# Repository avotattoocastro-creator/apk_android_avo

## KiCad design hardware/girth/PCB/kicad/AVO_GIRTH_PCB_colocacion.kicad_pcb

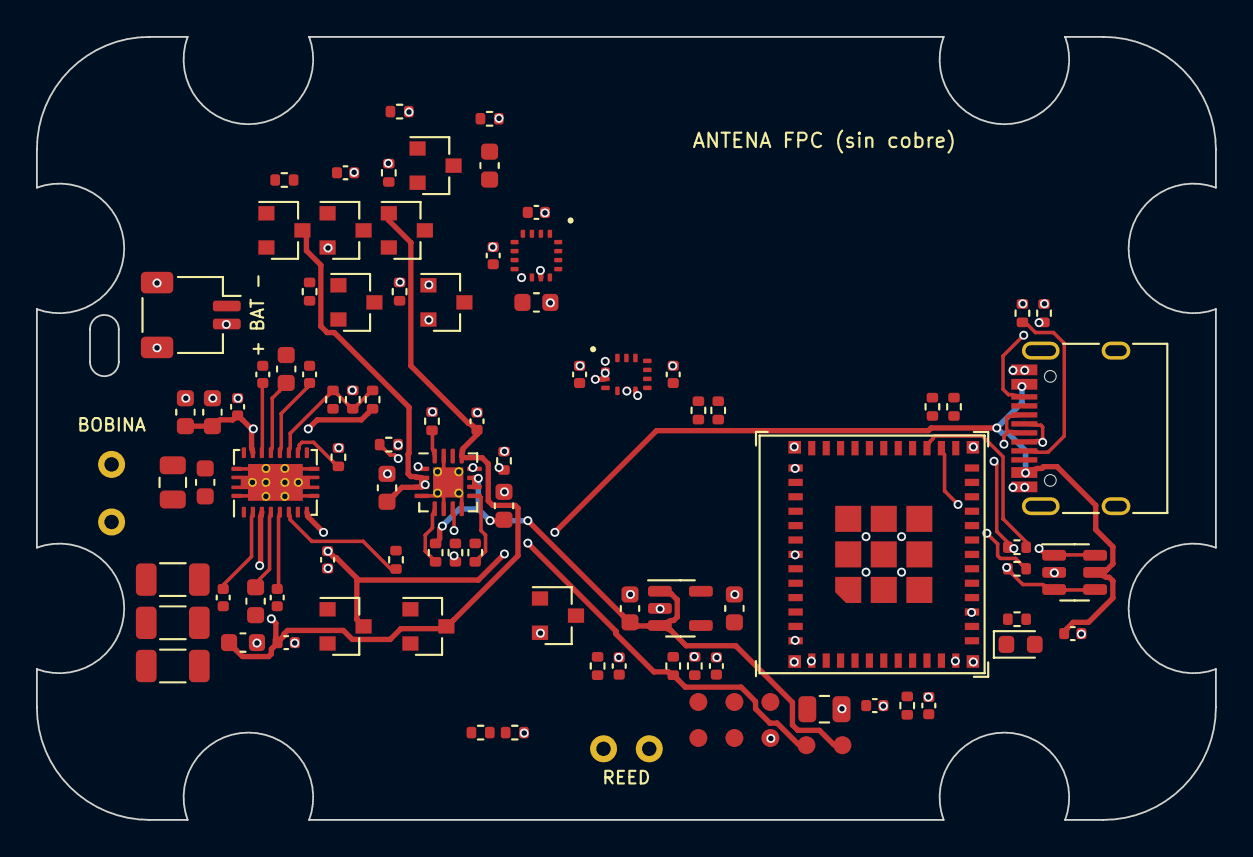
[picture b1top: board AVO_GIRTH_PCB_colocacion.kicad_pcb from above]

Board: 4 copper layers, 65.5 x 43.5 mm, 98 parts (0 on the bottom side), 55 nets.

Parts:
C1, C2: 100n C0G 50V; C_1206_3216Metric
C3: 47n C0G 50V; C_1206_3216Metric
C4: 2n2 C0G 50V; C_0805_2012Metric
C5: 1n C0G 50V; C_0603_1608Metric
C6, C9, C33: 10n 50V; C_0402_1005Metric
C7, C10: 470n 25V; C_0603_1608Metric
C8, C11: 22n 50V; C_0402_1005Metric
C12, C13, C15, C19, C20, C21, C22: 10u 25V; C_0603_1608Metric
C14, C16, C24, C27, C28, C31, C34: 100n; C_0402_1005Metric
C17, C18, C25, C26, C29: 1u; C_0402_1005Metric
C23: 22u 10V; C_0805_2012Metric
C30: 10u 6V3; C_0603_1608Metric
C40: 2u2; C_0603_1608Metric
C41: 220n; C_0402_1005Metric
D1: LED rojo; LED_0603_1608Metric
D10, D11, D12, D13: BAV70; SOT-23
J1: USB-C 16P; USB_C_Receptacle_HRO_TYPE-C-31-M-12
J2: BATERÍA 1S; JST_SH_SM02B-SRSS-TB_1x02-1MP_P1.00mm_Horizontal
L1: BOBINA Qi (1); WirePad_D1.5_Drill0.8
L2: BOBINA Qi (2); WirePad_D1.5_Drill0.8
Q1, Q2, Q10: AO3401A; SOT-23
Q11: AO3400A; SOT-23
Q16: 2N7002; SOT-23
R1: 330R; R_0402_1005Metric
R2: 200R; R_0402_1005Metric
R3: 20k; R_0402_1005Metric
R4, R8, R9, R10, R31, R43, R49: 100k; R_0402_1005Metric
R6, R7: 3k3; R_0402_1005Metric
R11, R12, R13: 10k; R_0402_1005Metric
R15: 1k; R_0402_1005Metric
R16, R17: 5k1; R_0402_1005Metric
R18, R19: 22R; R_0402_1005Metric
R20, R21: 4k7; R_0402_1005Metric
R32, R33, R40, R45, R50: 1M; R_0402_1005Metric
R41, R42: 10M; R_0402_1005Metric
R44: 220R; R_0402_1005Metric
RT1, RT2: NTC 10k B3380; R_0402_1005Metric
SW1: REED (1); WirePad_D1.5_Drill0.8
SW2: REED (2); WirePad_D1.5_Drill0.8
TP1: EN; TestPoint_Pad_D1.0mm
TP2: BOOT; TestPoint_Pad_D1.0mm
TP3: GND; TestPoint_Pad_D1.0mm
TP4: TXD0; TestPoint_Pad_D1.0mm
TP5: RXD0; TestPoint_Pad_D1.0mm
TP6: 3V3; TestPoint_Pad_D1.0mm
TP7: VBAT; TestPoint_Pad_D1.0mm
TP8: VSYS; TestPoint_Pad_D1.0mm
U1: BQ51013BRHLR; Texas_VQFN-RHL-20_ThermalVias
U2: BQ24072RGTR; VQFN-16-1EP_3x3mm_P0.5mm_EP1.68x1.68mm_ThermalVias
U3: RT9080-33GJ5; SOT-23-5
U4: ESP32-C3-MINI-1U-N4; ESP32-C3-MINI-1U
U5: LSM6DS3TR-C; ST_LGA-14L_2.5x3mm_P0.5mm
U6: USBLC6-2SC6; SOT-23-6
U7: MMC5983MA; MEMSIC_MMC5983MA_LGA-16_3x3mm_P0.5mm

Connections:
+3V3: C22.1, C23.1, C24.1, C27.1, C28.1, C29.1, C31.1, D1.2, R4.2, R9.2, R10.2, R11.2, R12.2, R13.2, R20.2, R21.2, R31.2, TP6.1, U3.5, U4.3, U5.5, U5.8, U5.12, U7.2, U7.4, U7.13
AD_SRC: Q1.2, Q2.2
BAT_ADC: C34.1, R32.2, R33.1, U4.6
BAT_RAW: J2.1, Q10.2, R40.1, SW2.1
BOOT: R12.1, TP2.1, U4.23
CC1: J1.A5, R16.1
CC2: J1.B5, R17.1
CHG_EN2: R8.1, U2.5
CHG_ILIM: R7.1, U2.12
CHG_ISET: R6.1, U2.16
CHG_PG: R9.1, U2.7, U4.18
CHG_STAT: R10.1, U2.9, U4.21
CHG_TS: RT2.1, U2.1
EN: C25.1, R11.1, TP1.1, U4.8
GND: C12.2, C13.2, C14.2, C15.2, C16.2, C17.2, C18.2, C19.2, C20.2, C21.2, C22.2, C23.2, C24.2, C25.2, C26.2, C27.2, C28.2, C29.2, C30.2, C31.2, C33.2, C34.2, C41.2, D13.1, D13.2, J1.A1, J1.A12, J1.B1, J1.B12, J1.S1, J2.2, J2.MP, Q11.2, Q16.2, R2.2, R6.2, R7.2, R16.2, R17.2, R33.2, R41.2, R42.2, R43.2, R45.2, R50.2, RT1.2, RT2.2, TP3.1, U1.1, U1.10, U1.11, U1.20, U1.21, U2.4, U2.6, U2.8, U2.15, U2.17, U3.2, U4.1, U4.2, U4.11, U4.14, U4.36, U4.37, U4.38, U4.39, U4.40, U4.41, U4.42, U4.43, U4.44, U4.45, U4.46, U4.47, U4.48, U4.49, U4.50, U4.51, U4.52, U4.53, U5.1, U5.2, U5.3, U5.6, U5.7, U6.2, U7.9, U7.11
I2C_SCL: R21.1, U4.5, U5.13, U7.1
I2C_SDA: R20.1, U4.20, U5.14, U7.16
IMU_INT: U4.12, U5.4
LED: R13.1, R15.1, U4.22
LED_K: D1.1, R15.2
MAG_CAP: C30.1, U7.10
PWR_G: C41.1, D10.3, D11.3, Q11.1, R42.1
PWR_HOLD: D10.2, R43.1, U4.19
PWR_PG: Q10.1, Q11.3, R40.2
QI_AC1: C1.2, C2.2, C3.2, C4.1, C5.1, C6.2, C7.2, C8.2, U1.2
QI_AC2: C4.2, C5.2, C9.2, C10.2, C11.2, L2.1, U1.19
QI_ADEN: Q1.1, Q2.1, U1.8
QI_BOOT1: C6.1, U1.3
QI_BOOT2: C9.1, U1.17
QI_CHG: R4.1, U1.7, U4.16
QI_CLAMP1: C7.1, U1.5
QI_CLAMP2: C10.1, U1.16
QI_COIL1: C1.1, C2.1, C3.1, L1.1
QI_COMM1: C8.1, U1.6
QI_COMM2: C11.1, U1.15
QI_FOD: R1.2, R2.1, R3.2, U1.14
QI_ILIM: R1.1, U1.12
QI_RECT: C12.1, C13.1, C14.1, R3.1, U1.18
QI_TS: RT1.1, U1.13
REED: C33.1, Q16.3, R31.1, U4.13
REED_C: D12.3, R44.1, R45.1
REED_CR: C40.1, R44.2
REED_G: Q16.1, R49.2, R50.1
REED_HI: D12.1, D12.2, R49.1, SW1.1
REED_PULSE: C40.2, D11.1, D11.2, D13.3, R41.1
U0RX: TP5.1, U4.30
U0TX: TP4.1, U4.31
USB_DM: R19.2, U4.26
USB_DM_C: J1.A7, J1.B7, R19.1, U6.3, U6.4
USB_DP: R18.2, U4.27
USB_DP_C: J1.A6, J1.B6, R18.1, U6.1, U6.6
VBAT: C20.1, Q10.3, R32.1, TP7.1, U2.2, U2.3
VBUS: C17.1, C26.1, J1.A4, J1.A9, J1.B4, J1.B9, Q1.3, U1.9, U6.5
VIN5: C15.1, C16.1, C18.1, D10.1, Q2.3, U1.4, U2.13
VSYS: C19.1, C21.1, R8.2, TP8.1, U2.10, U2.11, U3.1, U3.3

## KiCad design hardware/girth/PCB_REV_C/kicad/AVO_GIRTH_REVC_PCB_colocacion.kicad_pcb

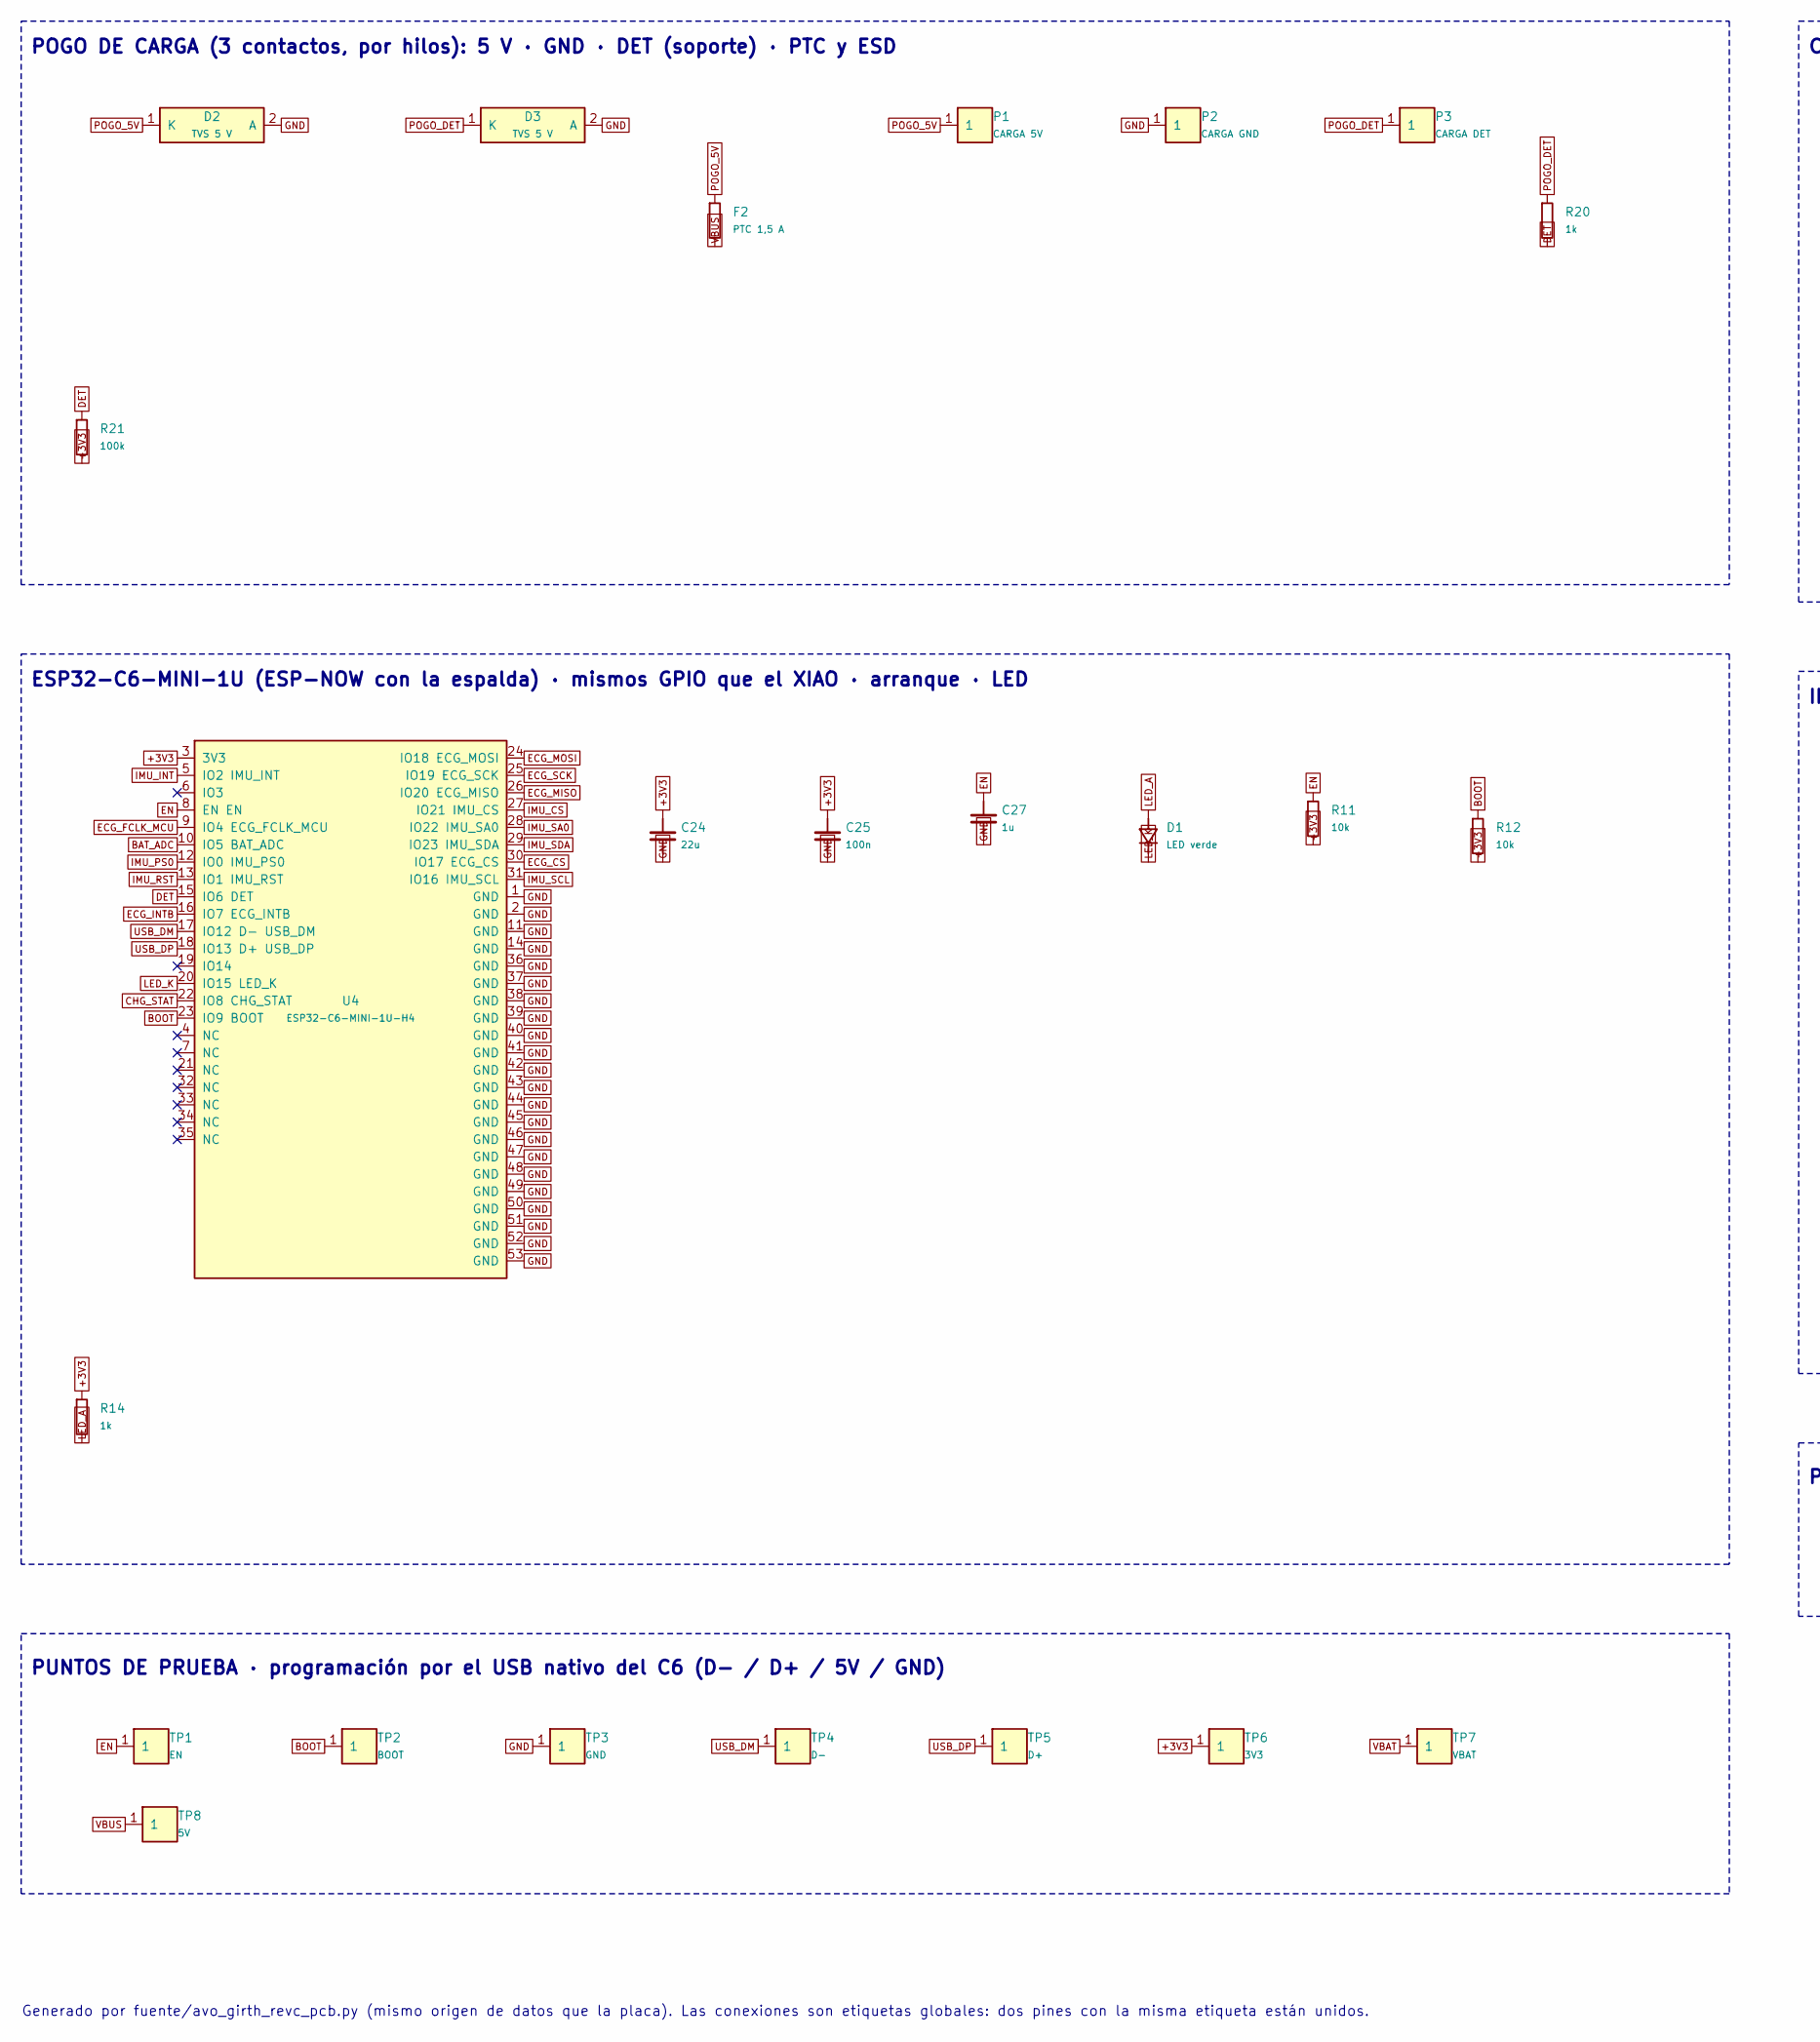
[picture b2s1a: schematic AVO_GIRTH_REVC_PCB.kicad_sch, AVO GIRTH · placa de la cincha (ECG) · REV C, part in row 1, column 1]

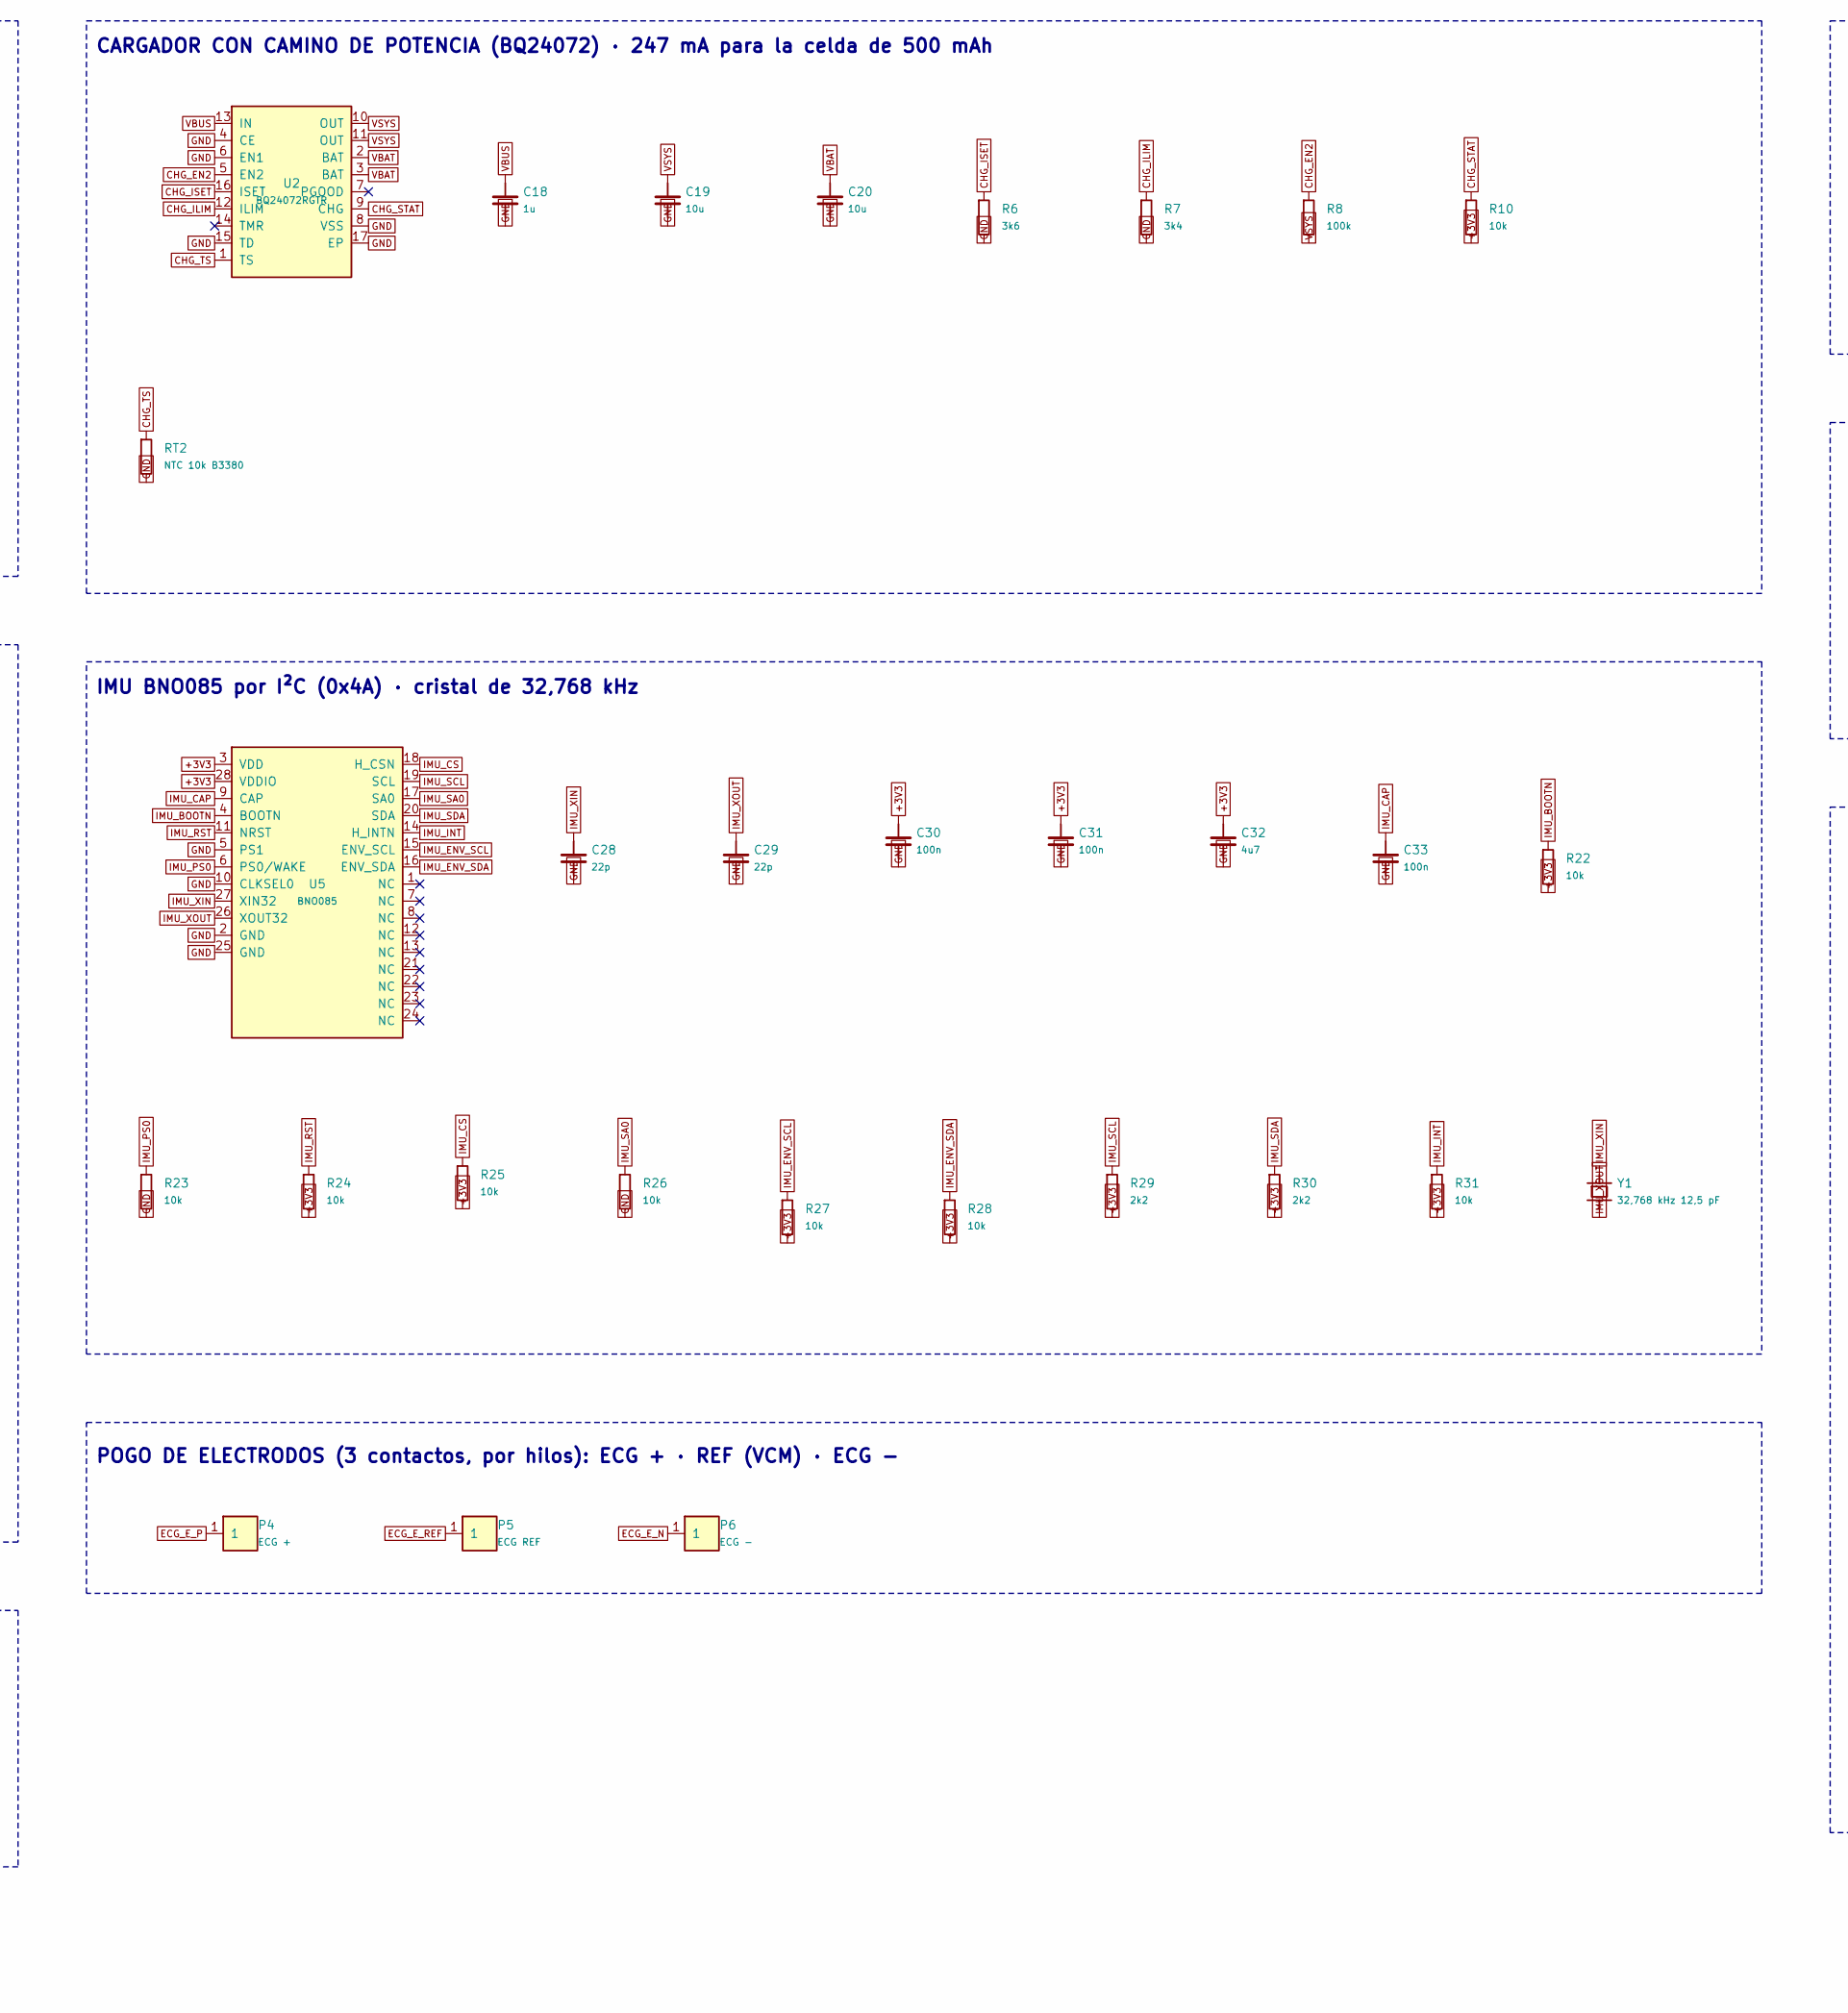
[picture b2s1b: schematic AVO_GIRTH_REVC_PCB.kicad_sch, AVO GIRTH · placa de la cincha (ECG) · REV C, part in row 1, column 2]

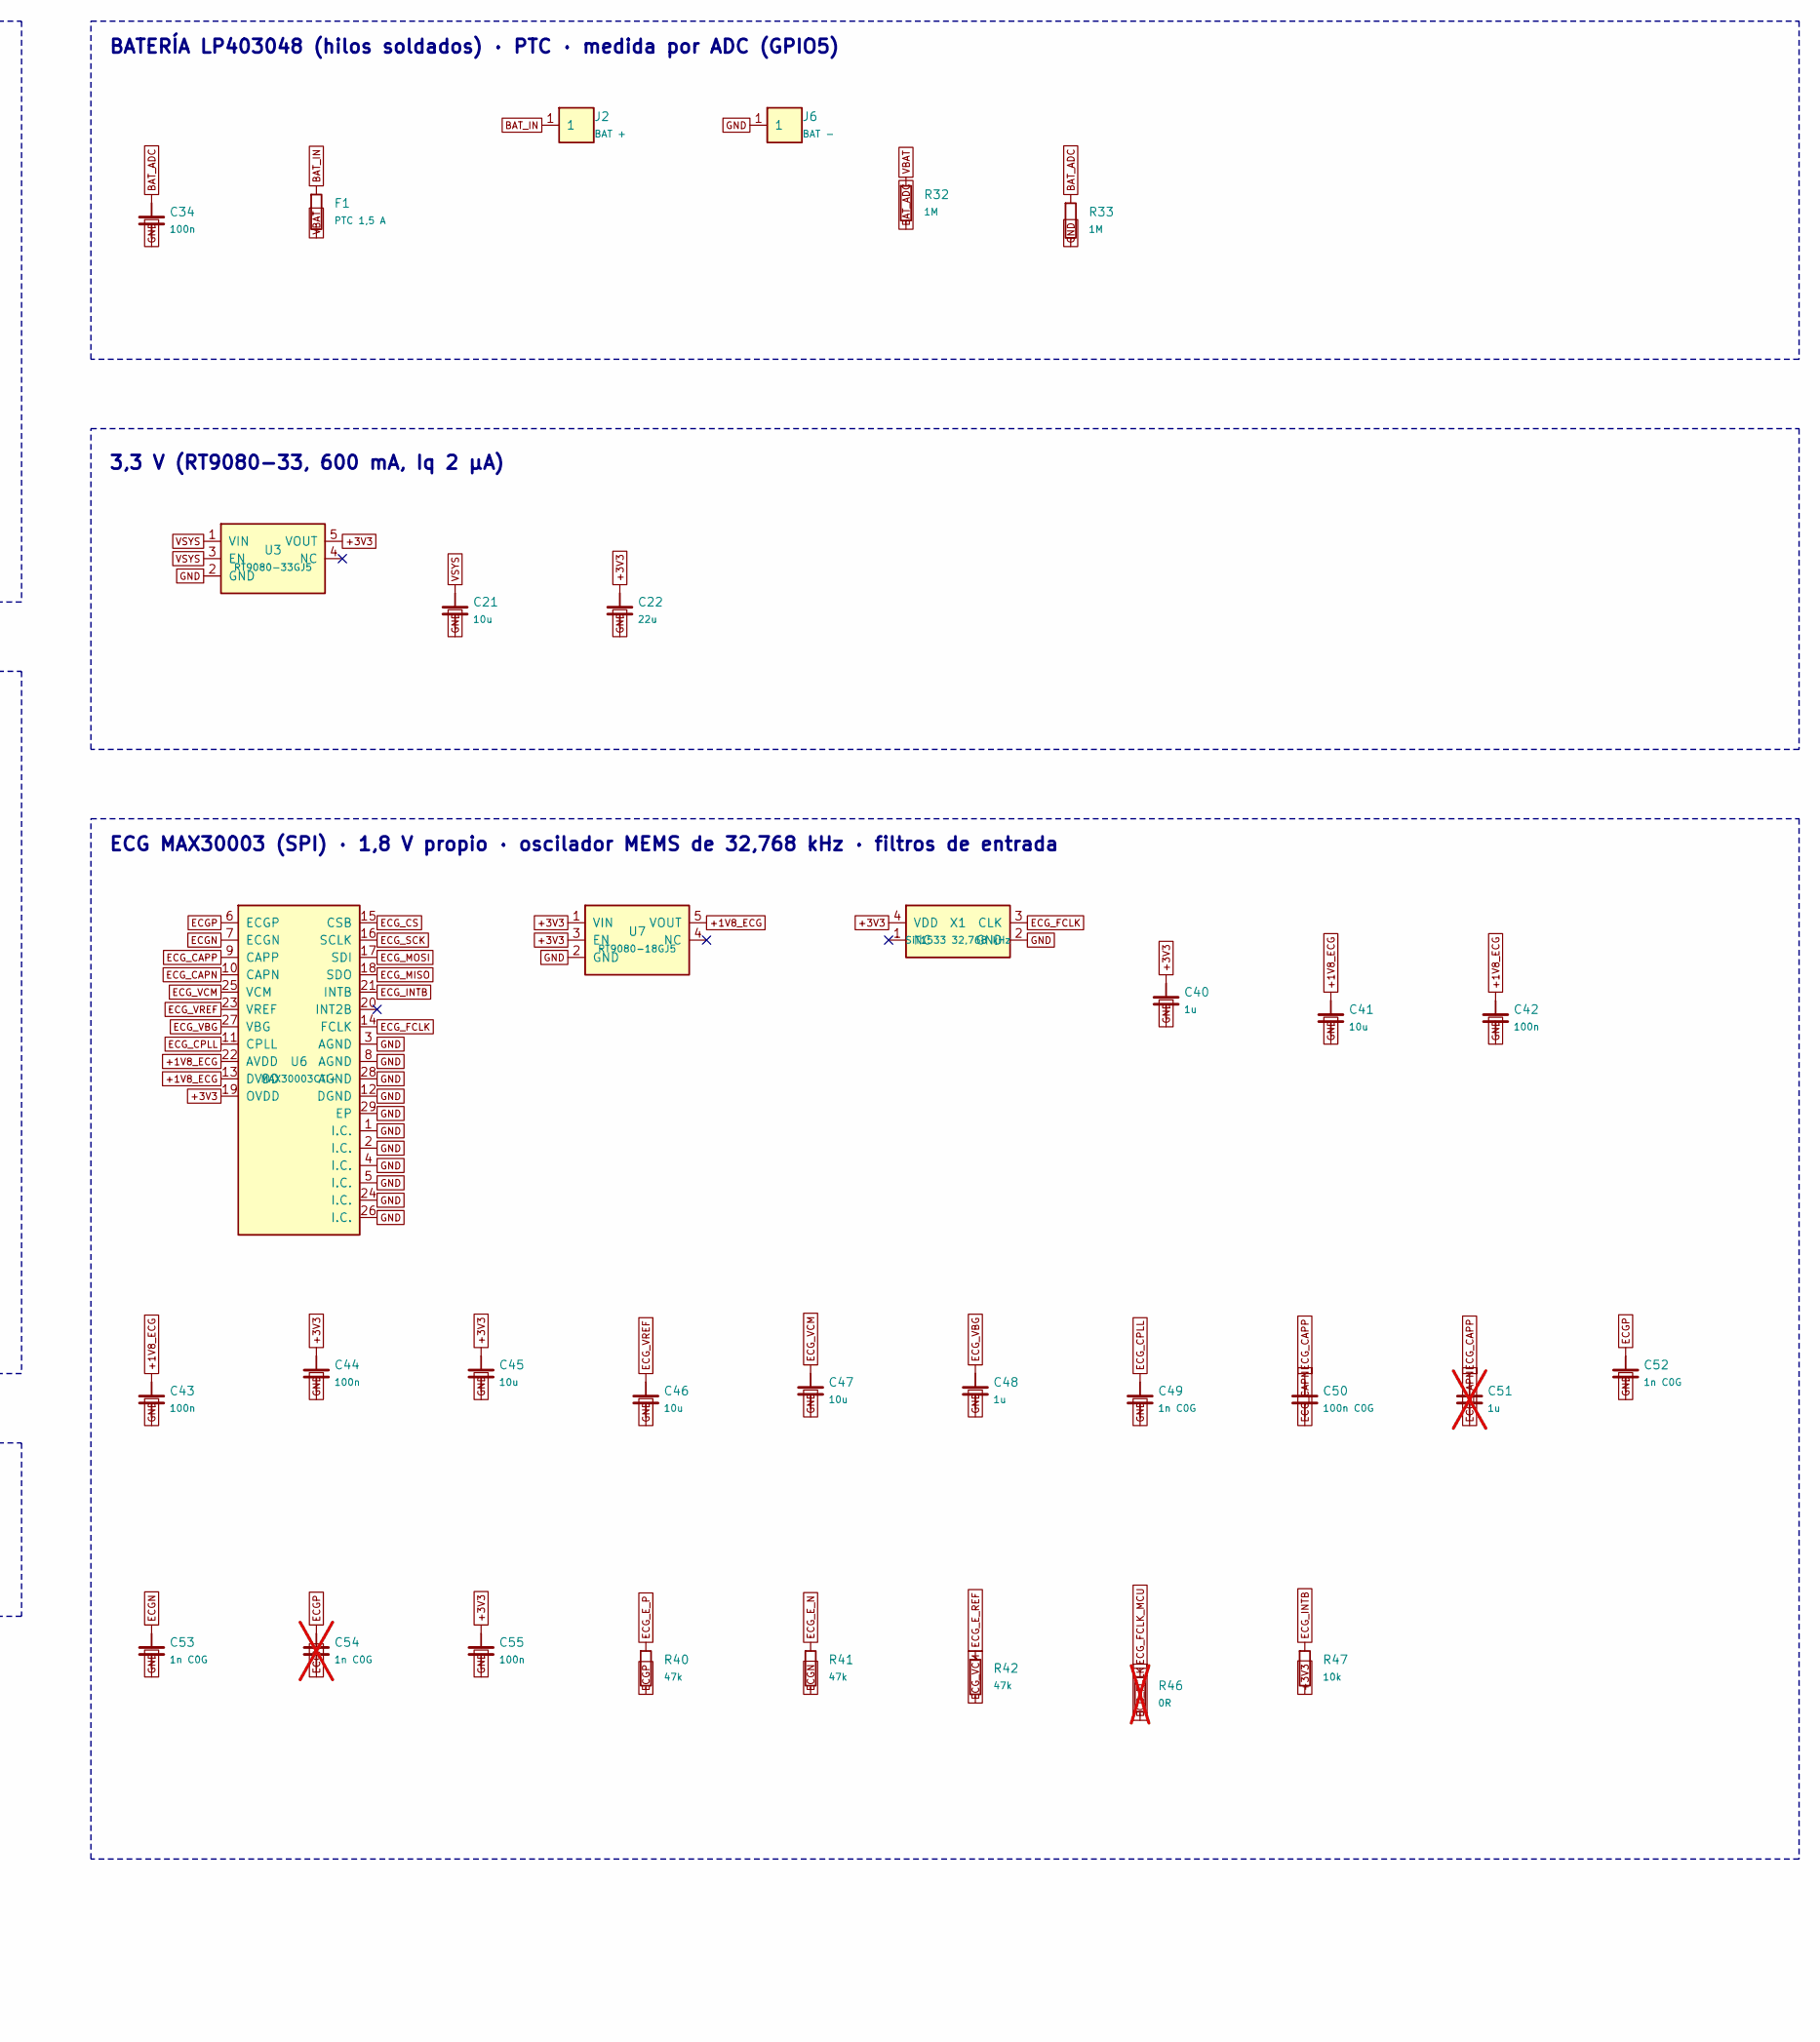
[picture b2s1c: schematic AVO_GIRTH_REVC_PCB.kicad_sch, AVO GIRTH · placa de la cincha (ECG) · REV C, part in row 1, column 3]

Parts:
C18, C27, C40, C48: 1u; C_0402_1005Metric; LCSC C52923
C19, C20, C21, C41, C45, C46, C47: 10u; C_0603_1608Metric; LCSC C96446
C22, C24: 22u; C_0805_2012Metric; LCSC C45783
C25, C30, C31, C33, C34, C42, C43, C44, C55: 100n; C_0402_1005Metric; LCSC C1525
C28, C29: 22p; C_0402_1005Metric; LCSC C1555
C32: 4u7; C_0603_1608Metric; LCSC C19666
C49, C52, C53: 1n C0G; C_0402_1005Metric; LCSC C53547
C50: 100n C0G; C_1206_3216Metric; LCSC C97946
C51: 1u; C_0402_1005Metric; LCSC C52923; not fitted
C54: 1n C0G; C_0402_1005Metric; LCSC C53547; not fitted
D1: LED verde; LED_0603_1608Metric; LCSC C2286
D2, D3: TVS 5 V; D_SOD-323; MPN PESD5V0S1BA; LCSC C2827694
F1, F2: PTC 1,5 A; Fuse_1206_3216Metric; MPN SMD1206P150TF; LCSC C20802
J2: BAT +; WirePad_D1.5_Drill0.8
J6: BAT -; WirePad_D1.5_Drill0.8
P1: CARGA 5V; WirePad_D1.5_Drill0.8
P2: CARGA GND; WirePad_D1.5_Drill0.8
P3: CARGA DET; WirePad_D1.5_Drill0.8
P4: ECG +; WirePad_D1.5_Drill0.8
P5: ECG REF; WirePad_D1.5_Drill0.8
P6: ECG -; WirePad_D1.5_Drill0.8
R6: 3k6; R_0402_1005Metric; LCSC C25891
R7: 3k4; R_0402_1005Metric; LCSC C4940
R8, R21: 100k; R_0402_1005Metric; LCSC C25741
R10, R11, R12, R22, R23, R24, R25, R26, R27, R28, R31, R47: 10k; R_0402_1005Metric; LCSC C25744
R14, R20: 1k; R_0402_1005Metric; LCSC C11702
R29, R30: 2k2; R_0402_1005Metric; LCSC C25879
R32, R33: 1M; R_0402_1005Metric; LCSC C26083
R40, R41, R42: 47k; R_0402_1005Metric; LCSC C25792
R46: 0R; R_0402_1005Metric; LCSC C17168; not fitted
RT2: NTC 10k B3380; R_0402_1005Metric; MPN NCP15XH103F03RC; LCSC C77131
TP1: EN; TestPoint_Pad_D1.0mm
TP2: BOOT; TestPoint_Pad_D1.0mm
TP3: GND; TestPoint_Pad_D1.0mm
TP4: D-; TestPoint_Pad_D1.0mm
TP5: D+; TestPoint_Pad_D1.0mm
TP6: 3V3; TestPoint_Pad_D1.0mm
TP7: VBAT; TestPoint_Pad_D1.0mm
TP8: 5V; TestPoint_Pad_D1.0mm
U2: BQ24072RGTR; VQFN-16-1EP_3x3mm_P0.5mm_EP1.68x1.68mm_ThermalVias; MPN BQ24072RGTR; LCSC C140288
U3: RT9080-33GJ5; SOT-23-5; MPN RT9080-33GJ5; LCSC C841192
U4: ESP32-C6-MINI-1U-H4; ESP32-C6-MINI-1U; MPN ESP32-C6-MINI-1U-H4 (alt. -N4); LCSC C20627095
U5: BNO085; CEVA_BNO08x_LGA-28_5.2x3.8mm_P0.5mm; MPN BNO085 (alt. BNO086); LCSC C5189642
U6: MAX30003CTI+; AVO_TQFN-28-1EP_5x5mm_P0.5mm_EP3.35mm; MPN MAX30003CTI+ (Analog Devices); LCSC C1519515
U7: RT9080-18GJ5; SOT-23-5; MPN RT9080-18GJ5; LCSC C426476
X1: SiT1533 32,768 kHz; AVO_SiT1533_2.0x1.2mm; MPN SIT1533AI-H4-DCC-32.768E (SiTime); LCSC C367058
Y1: 32,768 kHz 12,5 pF; Crystal_SMD_3215-2Pin_3.2x1.5mm; MPN Q13FC13500004; LCSC C32346

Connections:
+1V8_ECG: C41.1, C42.1, C43.1, U6.13 (DVDD), U6.22 (AVDD), U7.5 (VOUT)
+3V3: C22.1, C24.1, C25.1, C30.1, C31.1, C32.1, C40.1, C44.1, C45.1, C55.1, R10.2, R11.2, R12.2, R14.1, R21.2, R22.2, R24.2, R25.2, R27.2, R28.2, R29.2, R30.2, R31.2, R47.2, TP6.1, U3.5 (VOUT), U4.3 (3V3), U5.3 (VDD), U5.28 (VDDIO), U6.19 (OVDD), U7.1 (VIN), U7.3 (EN), X1.4 (VDD)
BAT_ADC: C34.1, R32.2, R33.1, U4.10 (IO5 BAT_ADC)
BAT_IN: F1.1, J2.1
BOOT: R12.1, TP2.1, U4.23 (IO9 BOOT)
CHG_EN2: R8.1, U2.5 (EN2)
CHG_ILIM: R7.1, U2.12 (ILIM)
CHG_ISET: R6.1, U2.16 (ISET)
CHG_STAT: R10.1, U2.9 (CHG), U4.22 (IO8 CHG_STAT)
CHG_TS: RT2.1, U2.1 (TS)
DET: R20.2, R21.1, U4.15 (IO6 DET)
ECGN: C53.1, C54.2, R41.2, U6.7 (ECGN)
ECGP: C52.1, C54.1, R40.2, U6.6 (ECGP)
ECG_CAPN: C50.2, C51.2, U6.10 (CAPN)
ECG_CAPP: C50.1, C51.1, U6.9 (CAPP)
ECG_CPLL: C49.1, U6.11 (CPLL)
ECG_CS: U4.30 (IO17 ECG_CS), U6.15 (CSB)
ECG_E_N: P6.1, R41.1
ECG_E_P: P4.1, R40.1
ECG_E_REF: P5.1, R42.1
ECG_FCLK: R46.2, U6.14 (FCLK), X1.3 (CLK)
ECG_FCLK_MCU: R46.1, U4.9 (IO4 ECG_FCLK_MCU)
ECG_INTB: R47.1, U4.16 (IO7 ECG_INTB), U6.21 (INTB)
ECG_MISO: U4.26 (IO20 ECG_MISO), U6.18 (SDO)
ECG_MOSI: U4.24 (IO18 ECG_MOSI), U6.17 (SDI)
ECG_SCK: U4.25 (IO19 ECG_SCK), U6.16 (SCLK)
ECG_VBG: C48.1, U6.27 (VBG)
ECG_VCM: C47.1, R42.2, U6.25 (VCM)
ECG_VREF: C46.1, U6.23 (VREF)
EN: C27.1, R11.1, TP1.1, U4.8 (EN EN)
GND: C18.2, C19.2, C20.2, C21.2, C22.2, C24.2, C25.2, C27.2, C28.2, C29.2, C30.2, C31.2, C32.2, C33.2, C34.2, C40.2, C41.2, C42.2, C43.2, C44.2, C45.2, C46.2, C47.2, C48.2, C49.2, C52.2, C53.2, C55.2, D2.2 (A), D3.2 (A), J6.1, P2.1, R6.2, R7.2, R23.2, R26.2, R33.2, RT2.2, TP3.1, U2.4 (CE), U2.6 (EN1), U2.8 (VSS), U2.15 (TD), U2.17 (EP), U3.2 (GND), U4.1 (GND), U4.2 (GND), U4.11 (GND), U4.14 (GND), U4.36 (GND), U4.37 (GND), U4.38 (GND), U4.39 (GND), U4.40 (GND), U4.41 (GND), U4.42 (GND), U4.43 (GND), U4.44 (GND), U4.45 (GND), U4.46 (GND), U4.47 (GND), U4.48 (GND), U4.49 (GND), U4.50 (GND), U4.51 (GND), U4.52 (GND), U4.53 (GND), U5.2 (GND), U5.5 (PS1), U5.10 (CLKSEL0), U5.25 (GND), U6.1 (I.C.), U6.2 (I.C.), U6.3 (AGND), U6.4 (I.C.), U6.5 (I.C.), U6.8 (AGND), U6.12 (DGND), U6.24 (I.C.), U6.26 (I.C.), U6.28 (AGND), U6.29 (EP), U7.2 (GND), X1.2 (GND)
IMU_BOOTN: R22.1, U5.4 (BOOTN)
IMU_CAP: C33.1, U5.9 (CAP)
IMU_CS: R25.1, U4.27 (IO21 IMU_CS), U5.18 (H_CSN)
IMU_ENV_SCL: R27.1, U5.15 (ENV_SCL)
IMU_ENV_SDA: R28.1, U5.16 (ENV_SDA)
IMU_INT: R31.1, U4.5 (IO2 IMU_INT), U5.14 (H_INTN)
IMU_PS0: R23.1, U4.12 (IO0 IMU_PS0), U5.6 (PS0/WAKE)
IMU_RST: R24.1, U4.13 (IO1 IMU_RST), U5.11 (NRST)
IMU_SA0: R26.1, U4.28 (IO22 IMU_SA0), U5.17 (SA0)
IMU_SCL: R29.1, U4.31 (IO16 IMU_SCL), U5.19 (SCL)
IMU_SDA: R30.1, U4.29 (IO23 IMU_SDA), U5.20 (SDA)
IMU_XIN: C28.1, U5.27 (XIN32), Y1.1
IMU_XOUT: C29.1, U5.26 (XOUT32), Y1.2
LED_A: D1.2 (A), R14.2
LED_K: D1.1 (K), U4.20 (IO15 LED_K)
POGO_5V: D2.1 (K), F2.1, P1.1
POGO_DET: D3.1 (K), P3.1, R20.1
USB_DM: TP4.1, U4.17 (IO12 D- USB_DM)
USB_DP: TP5.1, U4.18 (IO13 D+ USB_DP)
VBAT: C20.1, F1.2, R32.1, TP7.1, U2.2 (BAT), U2.3 (BAT)
VBUS: C18.1, F2.2, TP8.1, U2.13 (IN)
VSYS: C19.1, C21.1, R8.2, U2.10 (OUT), U2.11 (OUT), U3.1 (VIN), U3.3 (EN)

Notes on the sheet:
POGO DE CARGA (3 contactos, por hilos): 5 V · GND · DET (soporte) · PTC y ESD
CARGADOR CON CAMINO DE POTENCIA (BQ24072) · 247 mA para la celda de 500 mAh
3,3 V (RT9080-33, 600 mA, Iq 2 µA)
ESP32-C6-MINI-1U (ESP-NOW con la espalda) · mismos GPIO que el XIAO · arranque · LED
IMU BNO085 por I²C (0x4A) · cristal de 32,768 kHz
ECG MAX30003 (SPI) · 1,8 V propio · oscilador MEMS de 32,768 kHz · filtros de entrada
BATERÍA LP403048 (hilos soldados) · PTC · medida por ADC (GPIO5)
POGO DE ELECTRODOS (3 contactos, por hilos): ECG + · REF (VCM) · ECG −
PUNTOS DE PRUEBA · programación por el USB nativo del C6 (D− / D+ / 5V / GND)
Generado por fuente/avo_girth_revc_pcb.py (mismo origen de datos que la placa). Las conexiones son etiquetas globales: dos pines con la misma etiqueta están unidos.

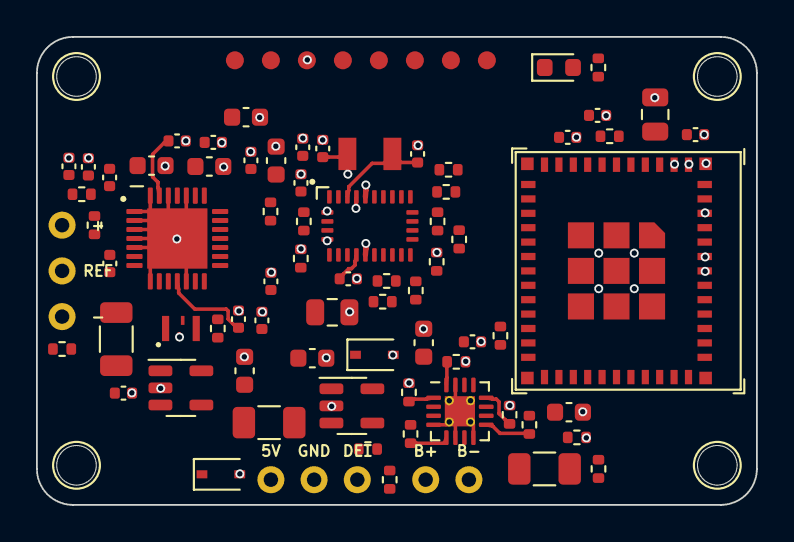
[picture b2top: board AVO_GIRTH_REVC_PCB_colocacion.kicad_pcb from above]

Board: 4 copper layers, 40.0 x 26.0 mm, 91 parts (0 on the bottom side), 53 nets.

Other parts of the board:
H1, H2, H3, H4: TALADRO M2; AVO_Taladro_NPTH_D2.2
